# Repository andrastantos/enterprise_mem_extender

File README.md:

A 512kB RAM expansion design for the Enterprise computer
===================================================================

This design can be used to add up to 512kB of RAM without to an Enterprise computer.
Jumpers can be used to determine the amount of RAM added (64k, 128k, 256k or 512k).

You can read up on whole project in detail here: https://www.modularcircuits.com/blog/2025/02/25/enterprise-128-a-blast-from-the-past/

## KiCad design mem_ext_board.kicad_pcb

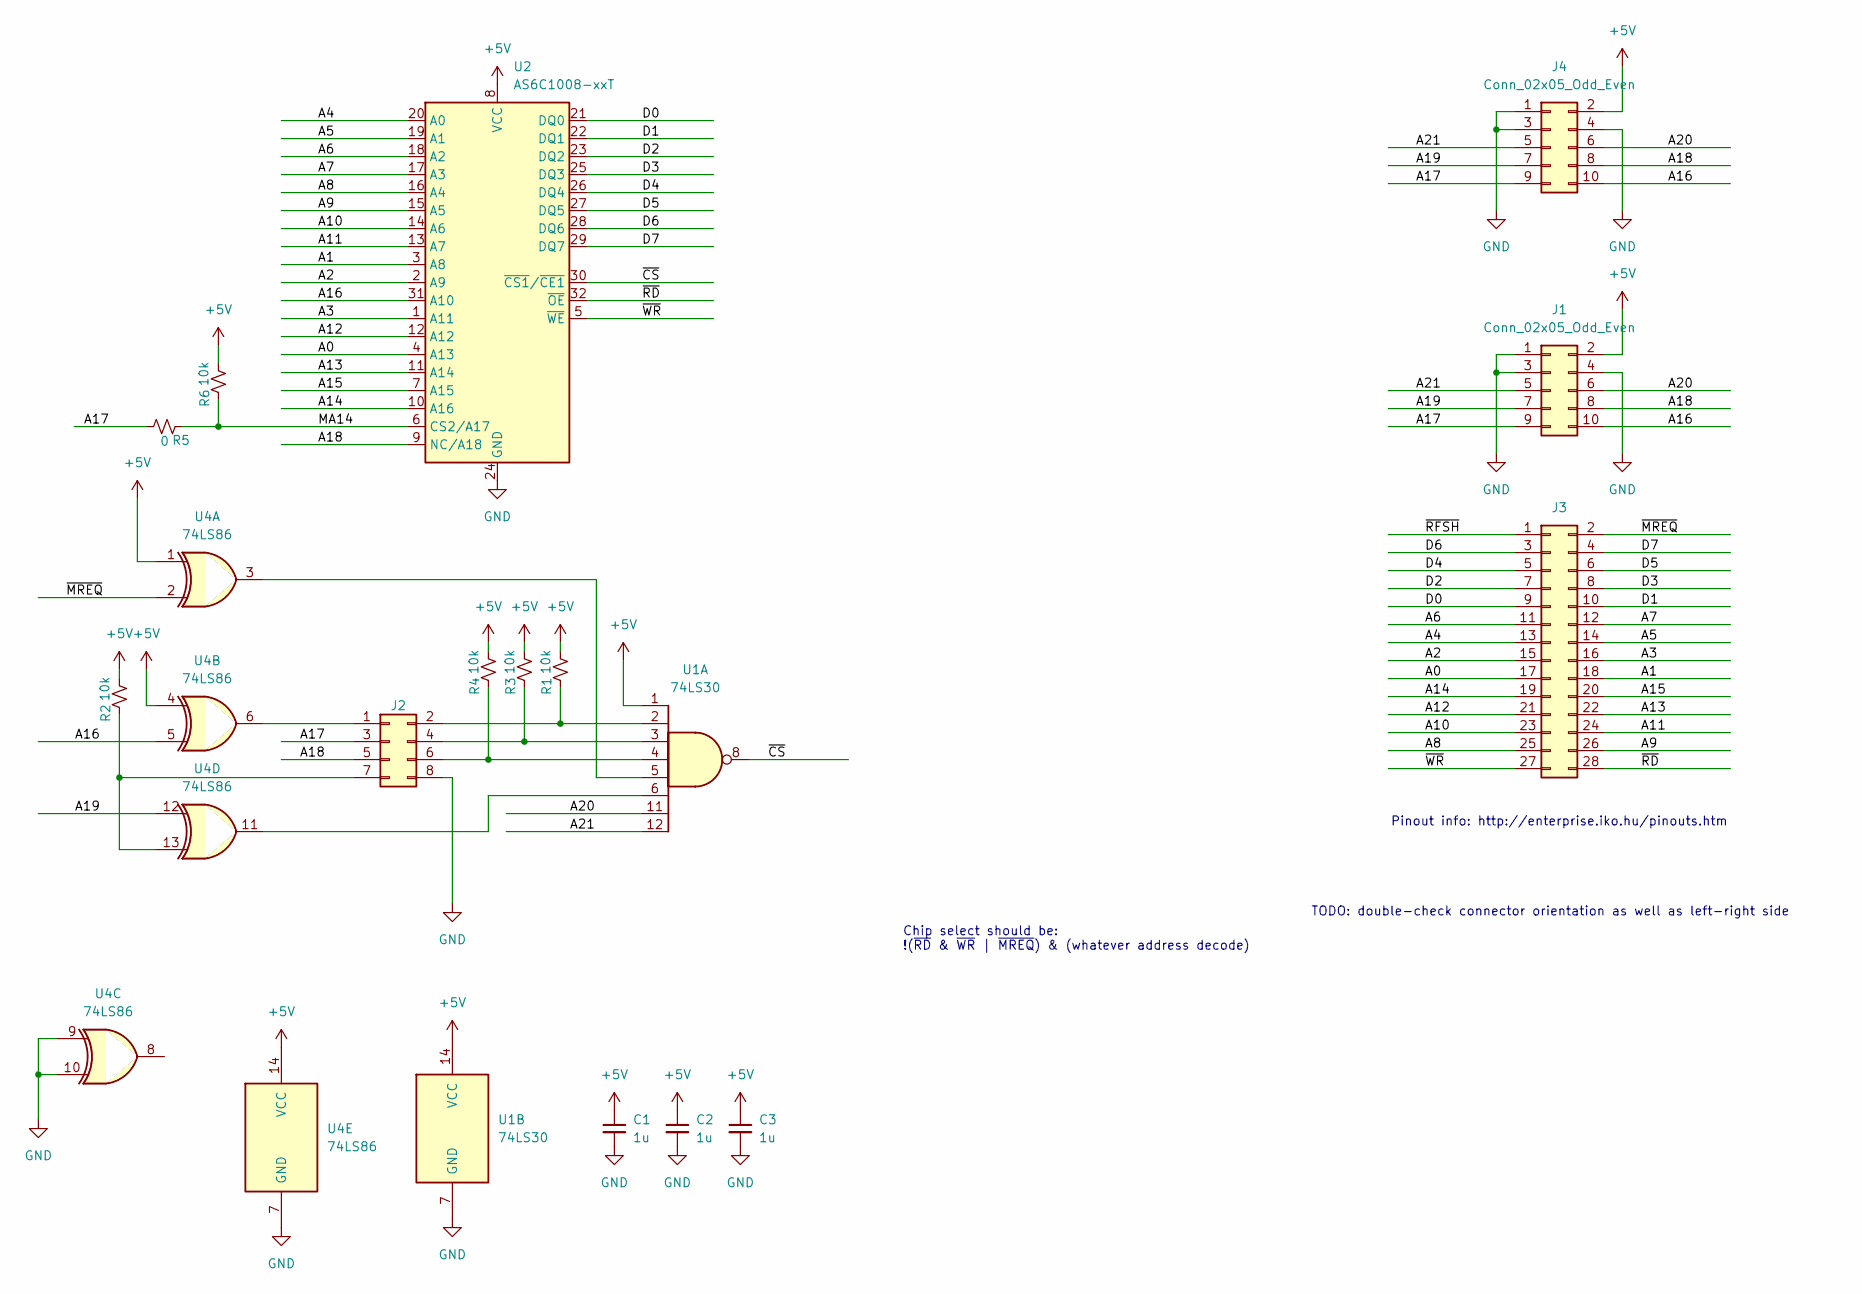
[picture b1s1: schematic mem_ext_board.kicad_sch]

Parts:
C1, C2, C3: 1u; C_0603_1608Metric_Pad1.08x0.95mm_HandSolder
J1: Conn_02x05_Odd_Even; PinHeader_2x05_P2.54mm_Vertical
J2: Conn_02x02_Odd_Even; PinHeader_2x04_P2.54mm_Vertical
J3: Conn_02x16_Row_Letter_First; PinSocket_2x14_P2.54mm_Vertical
J4: Conn_02x05_Odd_Even; PinSocket_2x05_P2.54mm_Vertical
R1, R2, R3, R4, R6: 10k; R_0603_1608Metric_Pad0.98x0.95mm_HandSolder
R5: 0; R_0603_1608Metric_Pad0.98x0.95mm_HandSolder
U1: 74LS30; SO-14_3.9x8.65mm_P1.27mm; mpn CD74HCT30M
U2: AS6C1008-xxT; TSOP-I-32_11-18.4x8mm_P0.5mm
U4: 74LS86; SO-14_3.9x8.65mm_P1.27mm; mpn CD74HCT86D

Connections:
+5V: C1.1, C2.1, C3.1, J1.2, J4.2, R1.1, R2.1, R3.1, R4.1, R6.1, U1.1, U1.14 (VCC), U2.8 (VCC), U4.1, U4.4, U4.14 (VCC)
/A0: J3.17, U2.4 (A13)
/A1: J3.18, U2.3 (A8)
/A2: J3.15, U2.2 (A9)
/A3: J3.16, U2.1 (A11)
/A4: J3.13, U2.20 (A0)
/A5: J3.14, U2.19 (A1)
/A6: J3.11, U2.18 (A2)
/A7: J3.12, U2.17 (A3)
/A8: J3.25, U2.16 (A4)
/A9: J3.26, U2.15 (A5)
/A10: J3.23, U2.14 (A6)
/A11: J3.24, U2.13 (A7)
/A12: J3.21, U2.12 (A12)
/A13: J3.22, U2.11 (A14)
/A14: J3.19, U2.10 (A16)
/A15: J3.20, U2.7 (A15)
/A16: J1.10, J4.10, U2.31 (A10), U4.5
/A17: J1.9, J2.3, J4.9, R5.1
/A18: J1.8, J2.5, J4.8, U2.9 (NC/A18)
/A19: J1.7, J4.7, U4.12
/A20: J1.6, J4.6, U1.11
/A21: J1.5, J4.5, U1.12
/D0: J3.9, U2.21 (DQ0)
/D1: J3.10, U2.22 (DQ1)
/D2: J3.7, U2.23 (DQ2)
/D3: J3.8, U2.25 (DQ3)
/D4: J3.5, U2.26 (DQ4)
/D5: J3.6, U2.27 (DQ5)
/D6: J3.3, U2.28 (DQ6)
/D7: J3.4, U2.29 (DQ7)
/MA14: R5.2, R6.2, U2.6 (CS2/A17)
/~CS: U1.8, U2.30 (~CS1/~CE1)
/~MREQ: J3.2, U4.2
/~RD: J3.28, U2.32 (~OE)
/~RFSH: J3.1
/~WR: J3.27, U2.5 (~WE)
GND: C1.2, C2.2, C3.2, J1.1, J1.3, J1.4, J2.8, J4.1, J4.3, J4.4, U1.7 (GND), U2.24 (GND), U4.7 (GND), U4.9, U4.10
unnamed: J2.1, U4.6
unnamed: J2.2, R1.2, U1.2
unnamed: J2.4, R3.2, U1.3
unnamed: J2.6, R4.2, U1.4
unnamed: J2.7, R2.2, U4.13
unnamed: U1.5, U4.3
unnamed: U1.6, U4.11

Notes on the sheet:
TODO: double-check connector orientation as well as left-right side
Pinout info: http://enterprise.iko.hu/pinouts.htm
Chip select should be: !(~{RD} & ~{WR} | ~{MREQ}) & (whatever address decode)

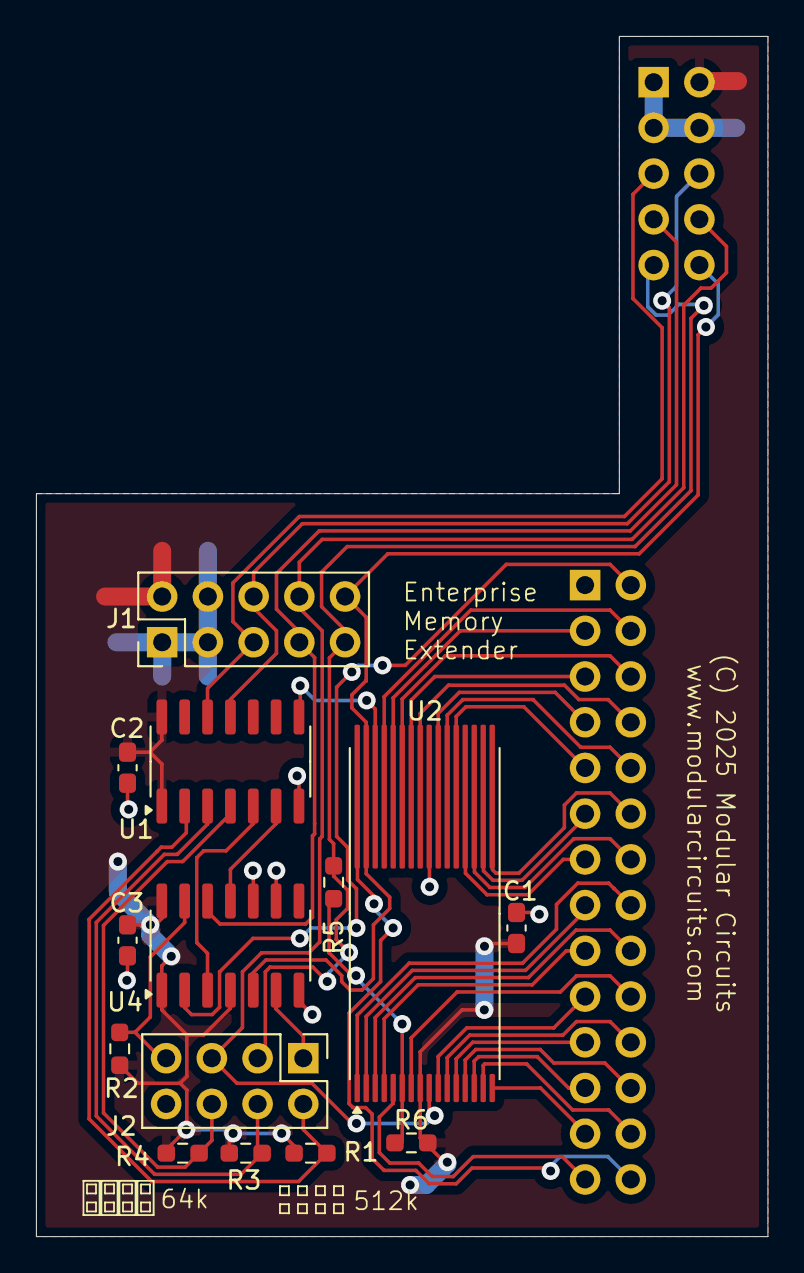
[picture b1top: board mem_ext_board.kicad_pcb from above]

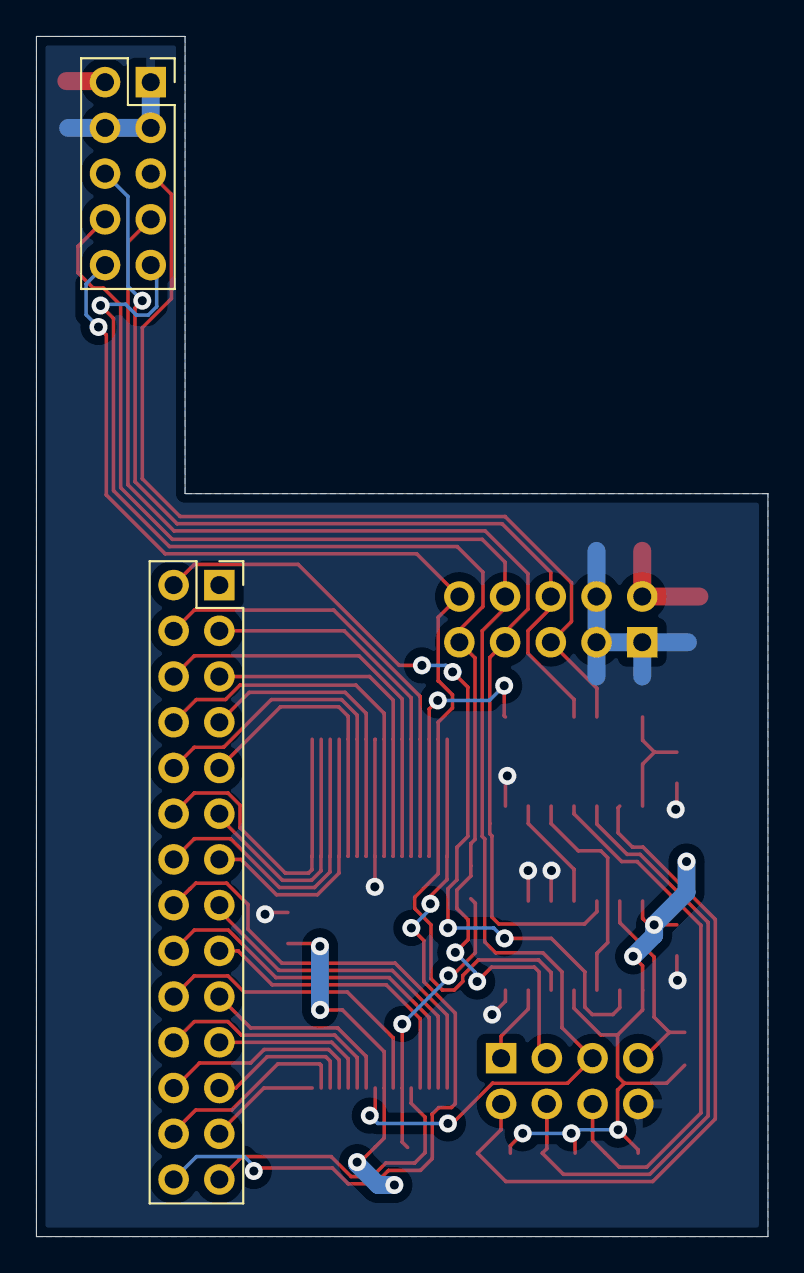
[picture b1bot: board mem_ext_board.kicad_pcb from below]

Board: 2 copper layers, 40.6 x 66.7 mm, 16 parts (2 on the bottom side), 44 nets.

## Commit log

2025-01-30 Added gitignore
2025-02-03 Updated board to hopefully final shape
2025-02-06 Moved connector to match mainboard layout.
2025-02-06 Added support for 1Mbit part, release package added.
2025-02-10 Universal memory footprint added: multiple package sizes are supported.
2025-02-23 Flipped jumper setting so that operation matches silk-screen.
2025-02-25 Added README

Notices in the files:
mem_ext_board.kicad_pcb:
(C) 2025 Modular Circuits
